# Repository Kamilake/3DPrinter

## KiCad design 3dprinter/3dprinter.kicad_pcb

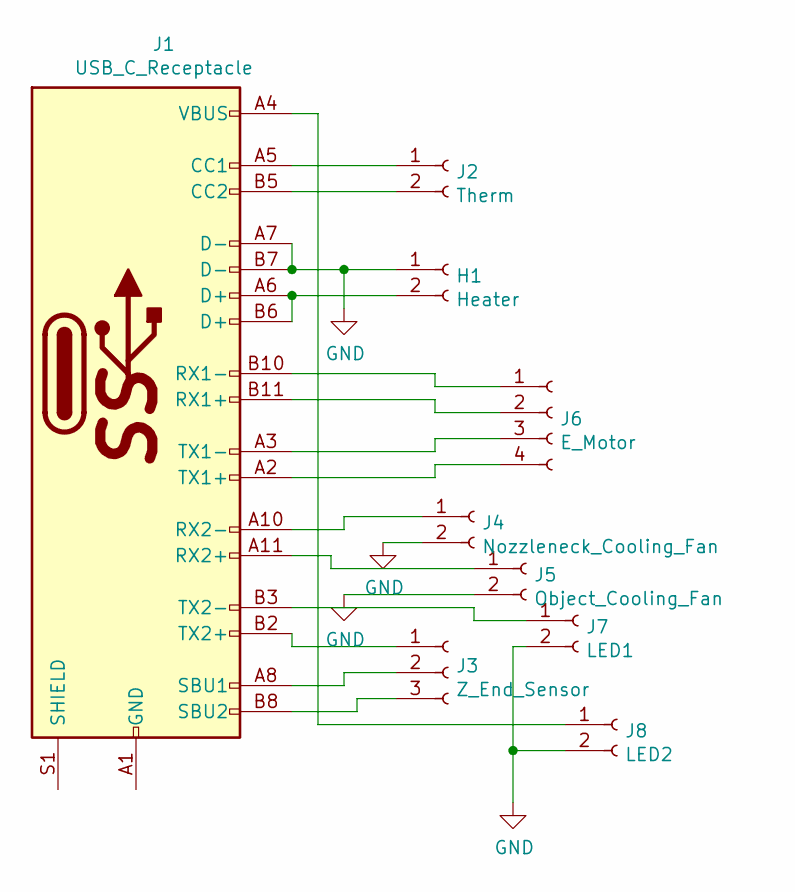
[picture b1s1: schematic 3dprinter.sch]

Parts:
H1: Heater; PhoenixContact_MSTBVA_2,5_2-G_1x02_P5.00mm_Vertical
J1: USB_C_Receptacle; USB_C_Receptacle_Amphenol_12401610E4-2A_CircularHoles
J2: Therm; JST_XH_B2B-XH-A_1x02_P2.50mm_Vertical
J3: Z_End_Sensor; JST_XH_B3B-XH-A_1x03_P2.50mm_Vertical
J4: Nozzleneck_Cooling_Fan; JST_XH_B2B-XH-A_1x02_P2.50mm_Vertical
J5: Object_Cooling_Fan; JST_XH_B2B-XH-A_1x02_P2.50mm_Vertical
J6: E_Motor; JST_XH_B4B-XH-A_1x04_P2.50mm_Vertical
J7: LED1; JST_XH_B2B-XH-A_1x02_P2.50mm_Vertical
J8: LED2; JST_XH_B2B-XH-A_1x02_P2.50mm_Vertical

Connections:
GND: H1.1, J1.A7 (D-), J1.B7 (D-), J4.2, J5.2, J7.2, J8.2
unnamed: H1.2, J1.A6 (D+), J1.B6 (D+)
unnamed: J1.A1 (GND), J1.A12 (GND), J1.B1 (GND), J1.B12 (GND)
unnamed: J1.A2 (TX1+), J6.4
unnamed: J1.A3 (TX1-), J6.3
unnamed: J1.A4 (VBUS), J1.A9 (VBUS), J1.B4 (VBUS), J1.B9 (VBUS), J8.1
unnamed: J1.A5 (CC1), J2.1
unnamed: J1.A8 (SBU1), J3.2
unnamed: J1.A10 (RX2-), J4.1
unnamed: J1.A11 (RX2+), J5.1
unnamed: J1.B2 (TX2+), J3.1
unnamed: J1.B3 (TX2-), J7.1
unnamed: J1.B5 (CC2), J2.2
unnamed: J1.B8 (SBU2), J3.3
unnamed: J1.B10 (RX1-), J6.1
unnamed: J1.B11 (RX1+), J6.2

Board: 2 copper layers, 9 parts (0 on the bottom side), 16 nets, no tracks yet.
